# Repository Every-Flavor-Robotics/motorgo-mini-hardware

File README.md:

# motorgo-mini-hardware
## This repo is the home of the hardware revisions for the MotorGo-mini!
### This is a condensed and specialized version of the MotorGo-Mini, featuring:
- Esp32s3 based system, compatible with ESPIDF or Arduino
- Wifi + BT
- Single channel of motor control
- Integrated MT6701 magenetic encoder on back of board
- DRV8316 TI motor controller with low-side current sense
- 3A continous 8A peak FOC motor controls
- RGB LED indicator
- USB PD x2 with power ORing to protect power sources
- 6P JST PH input: 5V-20V
- CAN bus over USB-C (experimental use of sideband signals in USB 3.2+)

### Its still in development, particularly USBPD seems to be malfunctioning.  But checkout the schematics, renders, use example, and photos of the real board!
### Full board Render:

### Example board + motor + rendering:

### Top Level Schematic (full color):

### USB Module Sub-Schematic:

### DRV8316 Sub-Schematic:

### RGB indicator:

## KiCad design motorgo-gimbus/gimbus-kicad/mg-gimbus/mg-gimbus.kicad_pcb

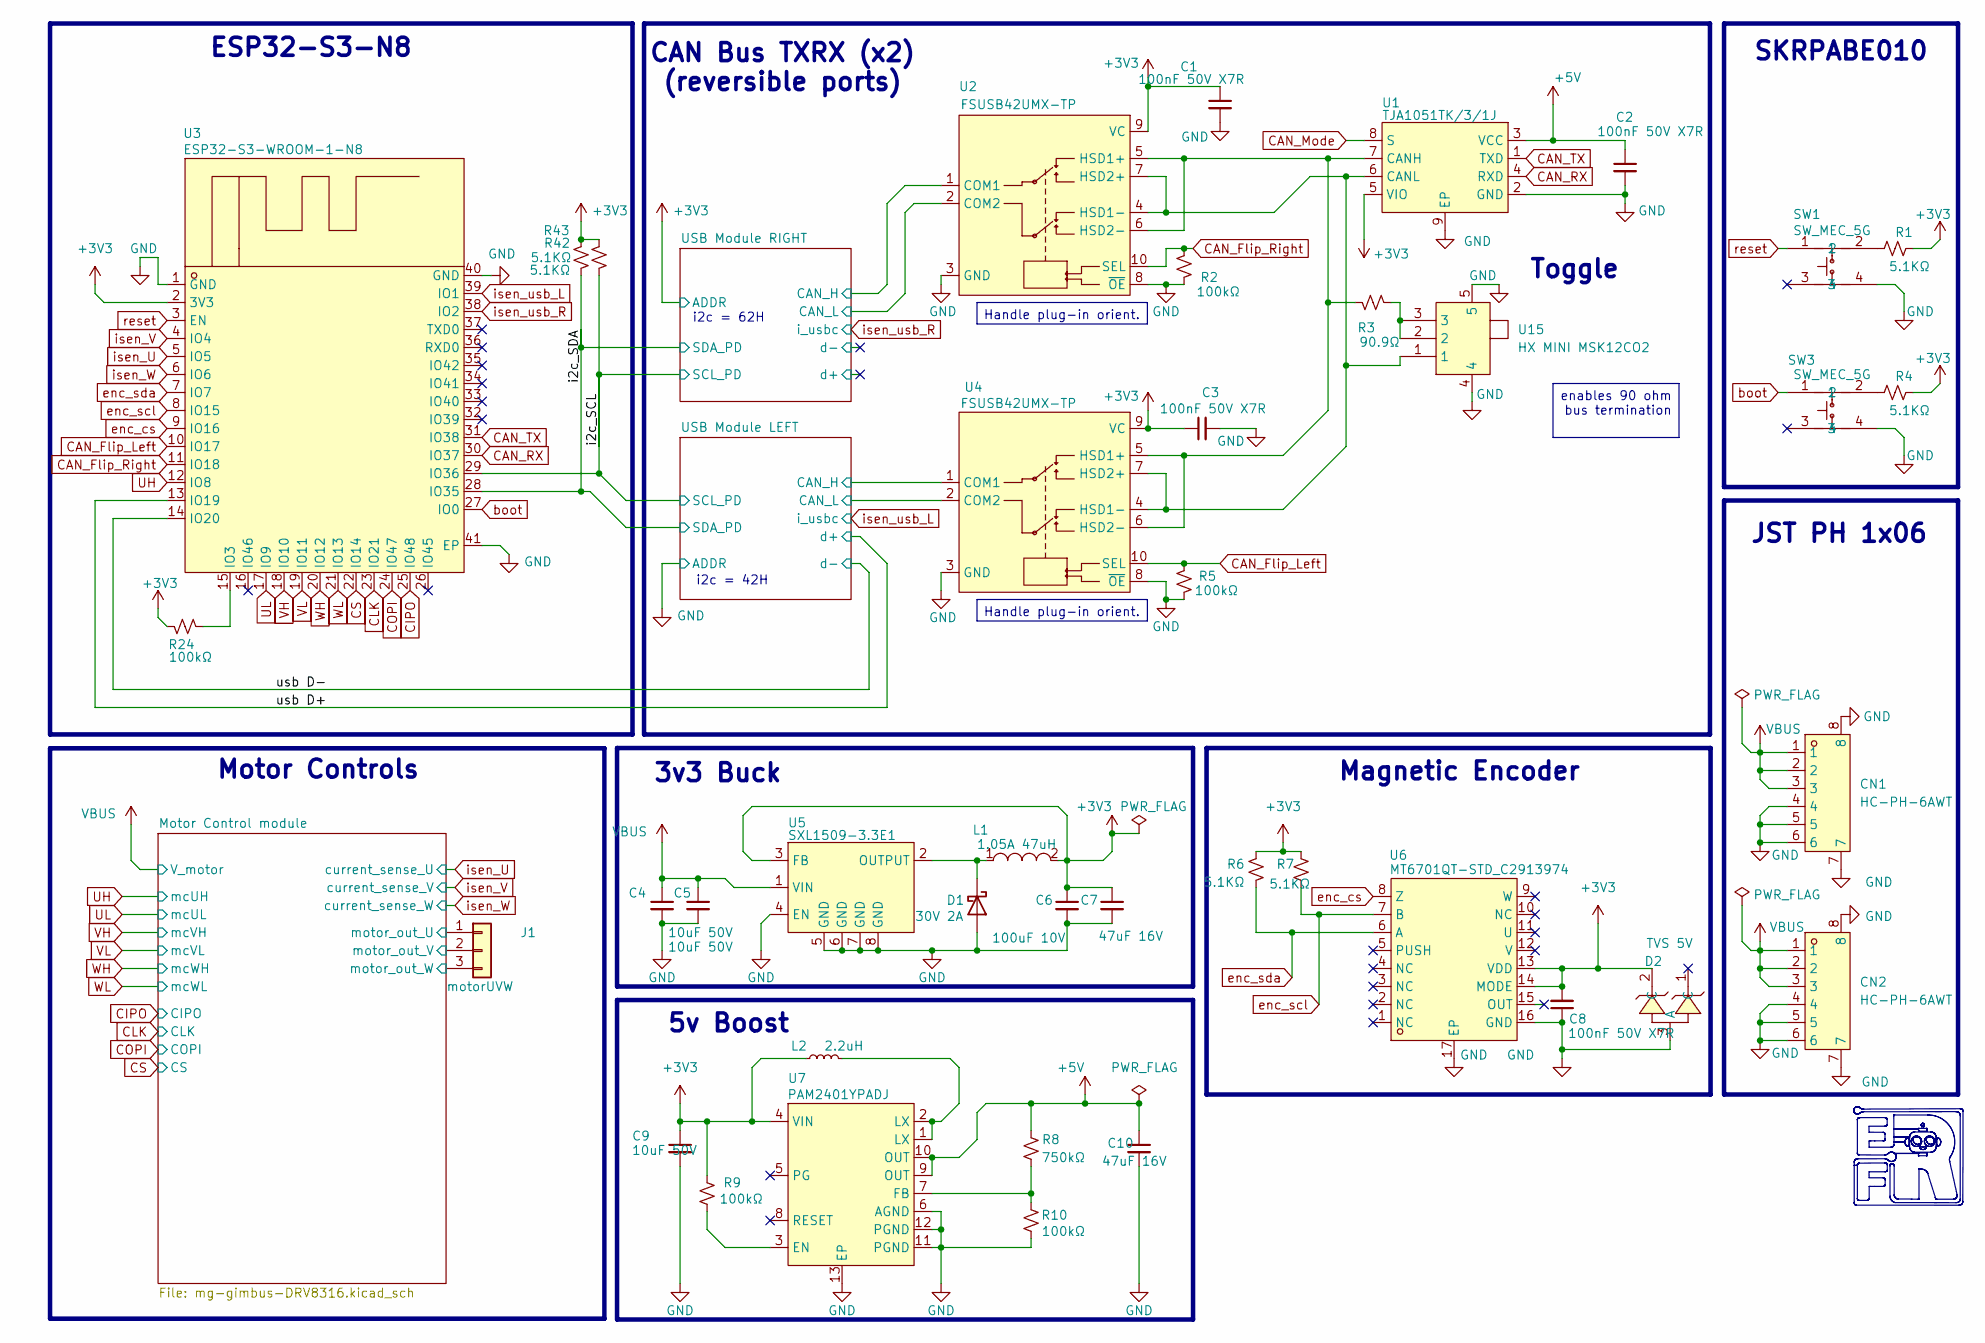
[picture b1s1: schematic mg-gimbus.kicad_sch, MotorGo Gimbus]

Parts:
C1, C2, C3, C8: 100nF 50V X7R; C_0402_1005Metric; LCSC Part C152814
C4, C5, C9: 10uF 50V; C_1206_3216Metric; LCSC Part C13585
C6: 100uF 10V; CAP-SMD_L7.3-W4.3_SA11CM470A19R55XXX; LCSC Part C42400366
C7, C10: 47uF 16V; C_1206_3216Metric; LCSC Part C172351
CN1, CN2: HC-PH-6AWT; CONN-SMD_6P-P2.00_HCTL_HC-PH-6AWT; LCSC Part C2845446
D1: 30V 2A; D_0603_1608Metric; LCSC Part C35621074
D2: TVS 5V; SOT-723_L1.2-W0.8-P0.40-LS1.2-BR; LCSC Part C896625
J1: motorUVW; Gimbus_Motor; LCSC Part n/a
L1: 1.05A 47uH; IND-SMD_L7.2-W6.6_GPSR07X0; LCSC Part C2929441
L2: 2.2uH; L_1008_2520Metric; LCSC Part C86092
R1, R4, R6, R7, R42, R43: 5.1KΩ; R_0402_1005Metric; LCSC Part C25905
R2, R5, R9, R10, R24: 100kΩ; R_0402_1005Metric; LCSC Part C25741
R3: 90.9Ω; R_0402_1005Metric; LCSC Part C208954
R8: 750kΩ; R_0402_1005Metric; LCSC Part C43291
SW1, SW3: SW_MEC_5G; KEY-SMD_4P-L4.2-W3.2-P2.20-LS4.6; LCSC Part C115360
U1: TJA1051TK/3/1J; HVSON-8_L3.0-W3.0-P0.65-BL-EP; LCSC Part C2875699
U2, U4: FSUSB42UMX-TP; XQFN-10_L1.8-W1.4-P0.40-TL; LCSC Part C42370490
U3: ESP32-S3-WROOM-1-N8; WIFIM-SMD_ESP32-S3-WROOM-1-N8; LCSC Part C2913198
U5: SXL1509-3.3E1; SOP-8_L4.9-W3.9-P1.27-LS6.0-BL-1; LCSC Part C33960106
U6: MT6701QT-STD_C2913974; QFN-16_L3.0-W3.0-P0.50-TL-EP1.7; LCSC Part C2913974
U7: PAM2401YPADJ; WDFN-12_L3.0-W3.0-P0.45-BL-EP; LCSC Part C490380
U15: HX MINI MSK12CO2; SW-SMD_MSK12CO2; LCSC Part C5149840

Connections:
+3V3: C1.1, C3.1, C6.1, C7.1, C8.2, C9.1, D2.2 (C), L1.2, L2.1, R1.2, R4.2, R6.1, R7.1, R9.2, R24.2, R42.1, R43.1, U1.5 (VIO), U2.9 (VC), U3.2 (3V3), U4.9 (VC), U5.3 (FB), U6.13 (VDD), U6.14 (MODE), U7.4 (VIN); also elsewhere on the board
+5V: C2.1, C10.1, R8.2, U1.3 (VCC), U7.9 (OUT), U7.10 (OUT)
/Motor Control module/motor_out_U: J1.1; also elsewhere on the board
/Motor Control module/motor_out_V: J1.2; also elsewhere on the board
/Motor Control module/motor_out_W: J1.3; also elsewhere on the board
/USB Module LEFT/CAN_H: U4.1 (COM1); also elsewhere on the board
/USB Module LEFT/CAN_L: U4.2 (COM2); also elsewhere on the board
/USB Module RIGHT/CAN_H: U2.1 (COM1); also elsewhere on the board
/USB Module RIGHT/CAN_L: U2.2 (COM2); also elsewhere on the board
/i2c_SCL: R42.2, U3.29 (IO36); also elsewhere on the board
/i2c_SDA: R43.2, U3.28 (IO35); also elsewhere on the board
/usb D+: U3.13 (IO19); also elsewhere on the board
/usb D-: U3.14 (IO20); also elsewhere on the board
CAN_Flip_Left: R5.2, U3.10 (IO17), U4.10 (SEL)
CAN_Flip_Right: R2.2, U2.10 (SEL), U3.11 (IO18)
CAN_Mode: U1.8 (S)
CAN_RX: U1.4 (RXD), U3.30 (IO37)
CAN_TX: U1.1 (TXD), U3.31 (IO38)
CIPO: U3.25 (IO48); also elsewhere on the board
CLK: U3.23 (IO21); also elsewhere on the board
COPI: U3.24 (IO47); also elsewhere on the board
CS: U3.22 (IO14); also elsewhere on the board
GND: C1.2, C2.2, C3.2, C4.2, C5.2, C6.2, C7.2, C8.1, C9.2, C10.2, CN1.4, CN1.5, CN1.6, CN1.7, CN1.8, CN2.4, CN2.5, CN2.6, CN2.7, CN2.8, D1.2 (A), D2.3 (A), R2.1, R5.1, R10.1, SW1.4, SW3.4, U1.2 (GND), U1.9 (EP), U2.3 (GND), U2.8 (~OE), U3.1 (GND), U3.40 (GND), U3.41 (EP), U4.3 (GND), U4.8 (~OE), U5.4 (EN), U5.5 (GND), U5.6 (GND), U5.7 (GND), U5.8 (GND), U6.16 (GND), U6.17 (EP), U7.6 (AGND), U7.11 (PGND), U7.12 (PGND), U7.13 (EP), U15.4, U15.5; also elsewhere on the board
unnamed: D1.1 (K), L1.1, U5.2 (OUTPUT)
unnamed: L2.2, U7.1 (LX), U7.2 (LX)
unnamed: R1.1, SW1.2
unnamed: R3.2, U15.2, U15.3
unnamed: R4.1, SW3.2
unnamed: R3.1, U1.7 (CANH), U2.5 (HSD1+), U2.6 (HSD2-), U4.5 (HSD1+), U4.6 (HSD2-)
unnamed: U1.6 (CANL), U2.4 (HSD1-), U2.7 (HSD2+), U4.4 (HSD1-), U4.7 (HSD2+), U15.1
unnamed: R24.1, U3.15 (IO3)
unnamed: R9.1, U7.3 (EN)
unnamed: R8.1, R10.2, U7.7 (FB)
UH: U3.12 (IO8); also elsewhere on the board
UL: U3.17 (IO9); also elsewhere on the board
VBUS: C4.1, C5.1, CN1.1, CN1.2, CN1.3, CN2.1, CN2.2, CN2.3, U5.1 (VIN); also elsewhere on the board
VH: U3.18 (IO10); also elsewhere on the board
VL: U3.19 (IO11); also elsewhere on the board
WH: U3.20 (IO12); also elsewhere on the board
WL: U3.21 (IO13); also elsewhere on the board
boot: SW3.1, U3.27 (IO0)
enc_cs: U3.9 (IO16), U6.8 (Z)
enc_scl: R7.2, U3.8 (IO15), U6.7 (B)
enc_sda: R6.2, U3.7 (IO7), U6.6 (A)
isen_U: U3.5 (IO5); also elsewhere on the board
isen_V: U3.4 (IO4); also elsewhere on the board
isen_W: U3.6 (IO6); also elsewhere on the board
isen_usb_L: U3.39 (IO1); also elsewhere on the board
isen_usb_R: U3.38 (IO2); also elsewhere on the board
reset: SW1.1, U3.3 (EN)

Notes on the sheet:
i2c = 62H
ESP32-S3-N8
i2c = 42H
Toggle
JST PH 1x06
Magnetic Encoder
5v Boost
SKRPABE010
CAN Bus TXRX (x2) (reversible ports)
3v3 Buck
Motor Controls
Handle plug-in orient.
enables 90 ohm bus termination

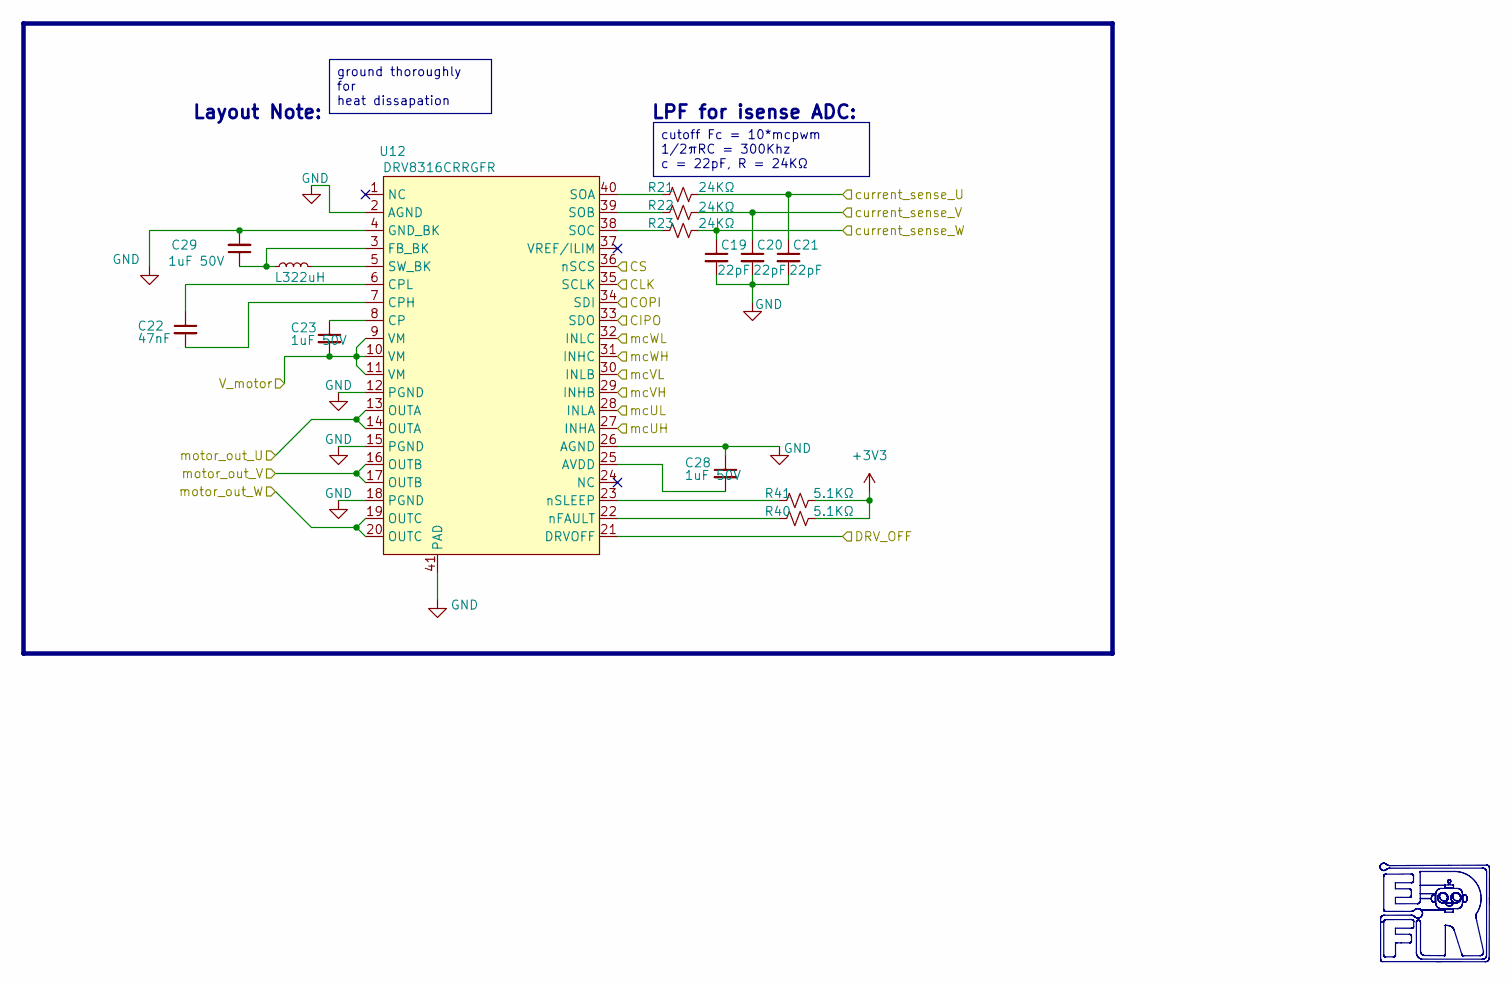
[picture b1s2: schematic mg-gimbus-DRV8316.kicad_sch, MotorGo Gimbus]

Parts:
C19, C20, C21: 22pF; C_0402_1005Metric; LCSC Part C76960
C22: 47nF; C_0402_1005Metric; LCSC Part C82219
C23, C28, C29: 1uF 50V; C_0805_2012Metric; LCSC Part C28323
L3: 22uH; L_0603_1608Metric; LCSC Part C383393
R21, R22, R23: 24KΩ; R_0402_1005Metric; LCSC Part C25769
R40, R41: 5.1KΩ; R_0402_1005Metric; LCSC Part C25905
U12: DRV8316CRRGFR; VQFN-40_L7.0-W5.0-P0.50-BL-EP5.7; LCSC Part C5447274

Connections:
+3V3: R40.2, R41.2; also elsewhere on the board
/Motor Control module/DRV_OFF: U12.21 (DRVOFF)
/Motor Control module/motor_out_U: U12.13 (OUTA), U12.14 (OUTA); also elsewhere on the board
/Motor Control module/motor_out_V: U12.16 (OUTB), U12.17 (OUTB); also elsewhere on the board
/Motor Control module/motor_out_W: U12.19 (OUTC), U12.20 (OUTC); also elsewhere on the board
CIPO: U12.33 (SDO); also elsewhere on the board
CLK: U12.35 (SCLK); also elsewhere on the board
COPI: U12.34 (SDI); also elsewhere on the board
CS: U12.36 (nSCS); also elsewhere on the board
GND: C19.2, C20.2, C21.2, C28.1, C29.2, U12.2 (AGND), U12.4 (GND_BK), U12.12 (PGND), U12.15 (PGND), U12.18 (PGND), U12.26 (AGND), U12.41 (PAD); also elsewhere on the board
unnamed: C28.2, U12.25 (AVDD)
unnamed: C23.1, U12.8 (CP)
unnamed: C22.2, U12.7 (CPH)
unnamed: C22.1, U12.6 (CPL)
unnamed: C29.1, L3.1, U12.3 (FB_BK)
unnamed: R21.1, U12.40 (SOA)
unnamed: R22.1, U12.39 (SOB)
unnamed: R23.1, U12.38 (SOC)
unnamed: L3.2, U12.5 (SW_BK)
unnamed: R40.1, U12.22 (nFAULT)
unnamed: R41.1, U12.23 (nSLEEP)
UH: U12.27 (INHA); also elsewhere on the board
UL: U12.28 (INLA); also elsewhere on the board
VBUS: C23.2, U12.9 (VM), U12.10 (VM), U12.11 (VM); also elsewhere on the board
VH: U12.29 (INHB); also elsewhere on the board
VL: U12.30 (INLB); also elsewhere on the board
WH: U12.31 (INHC); also elsewhere on the board
WL: U12.32 (INLC); also elsewhere on the board
isen_U: C21.1, R21.2; also elsewhere on the board
isen_V: C20.1, R22.2; also elsewhere on the board
isen_W: C19.1, R23.2; also elsewhere on the board

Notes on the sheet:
Layout Note:
LPF for isense ADC:
cutoff Fc = 10*mcpwm 1/2πRC = 300Khz c = 22pF, R = 24KΩ
ground thoroughly for heat dissapation

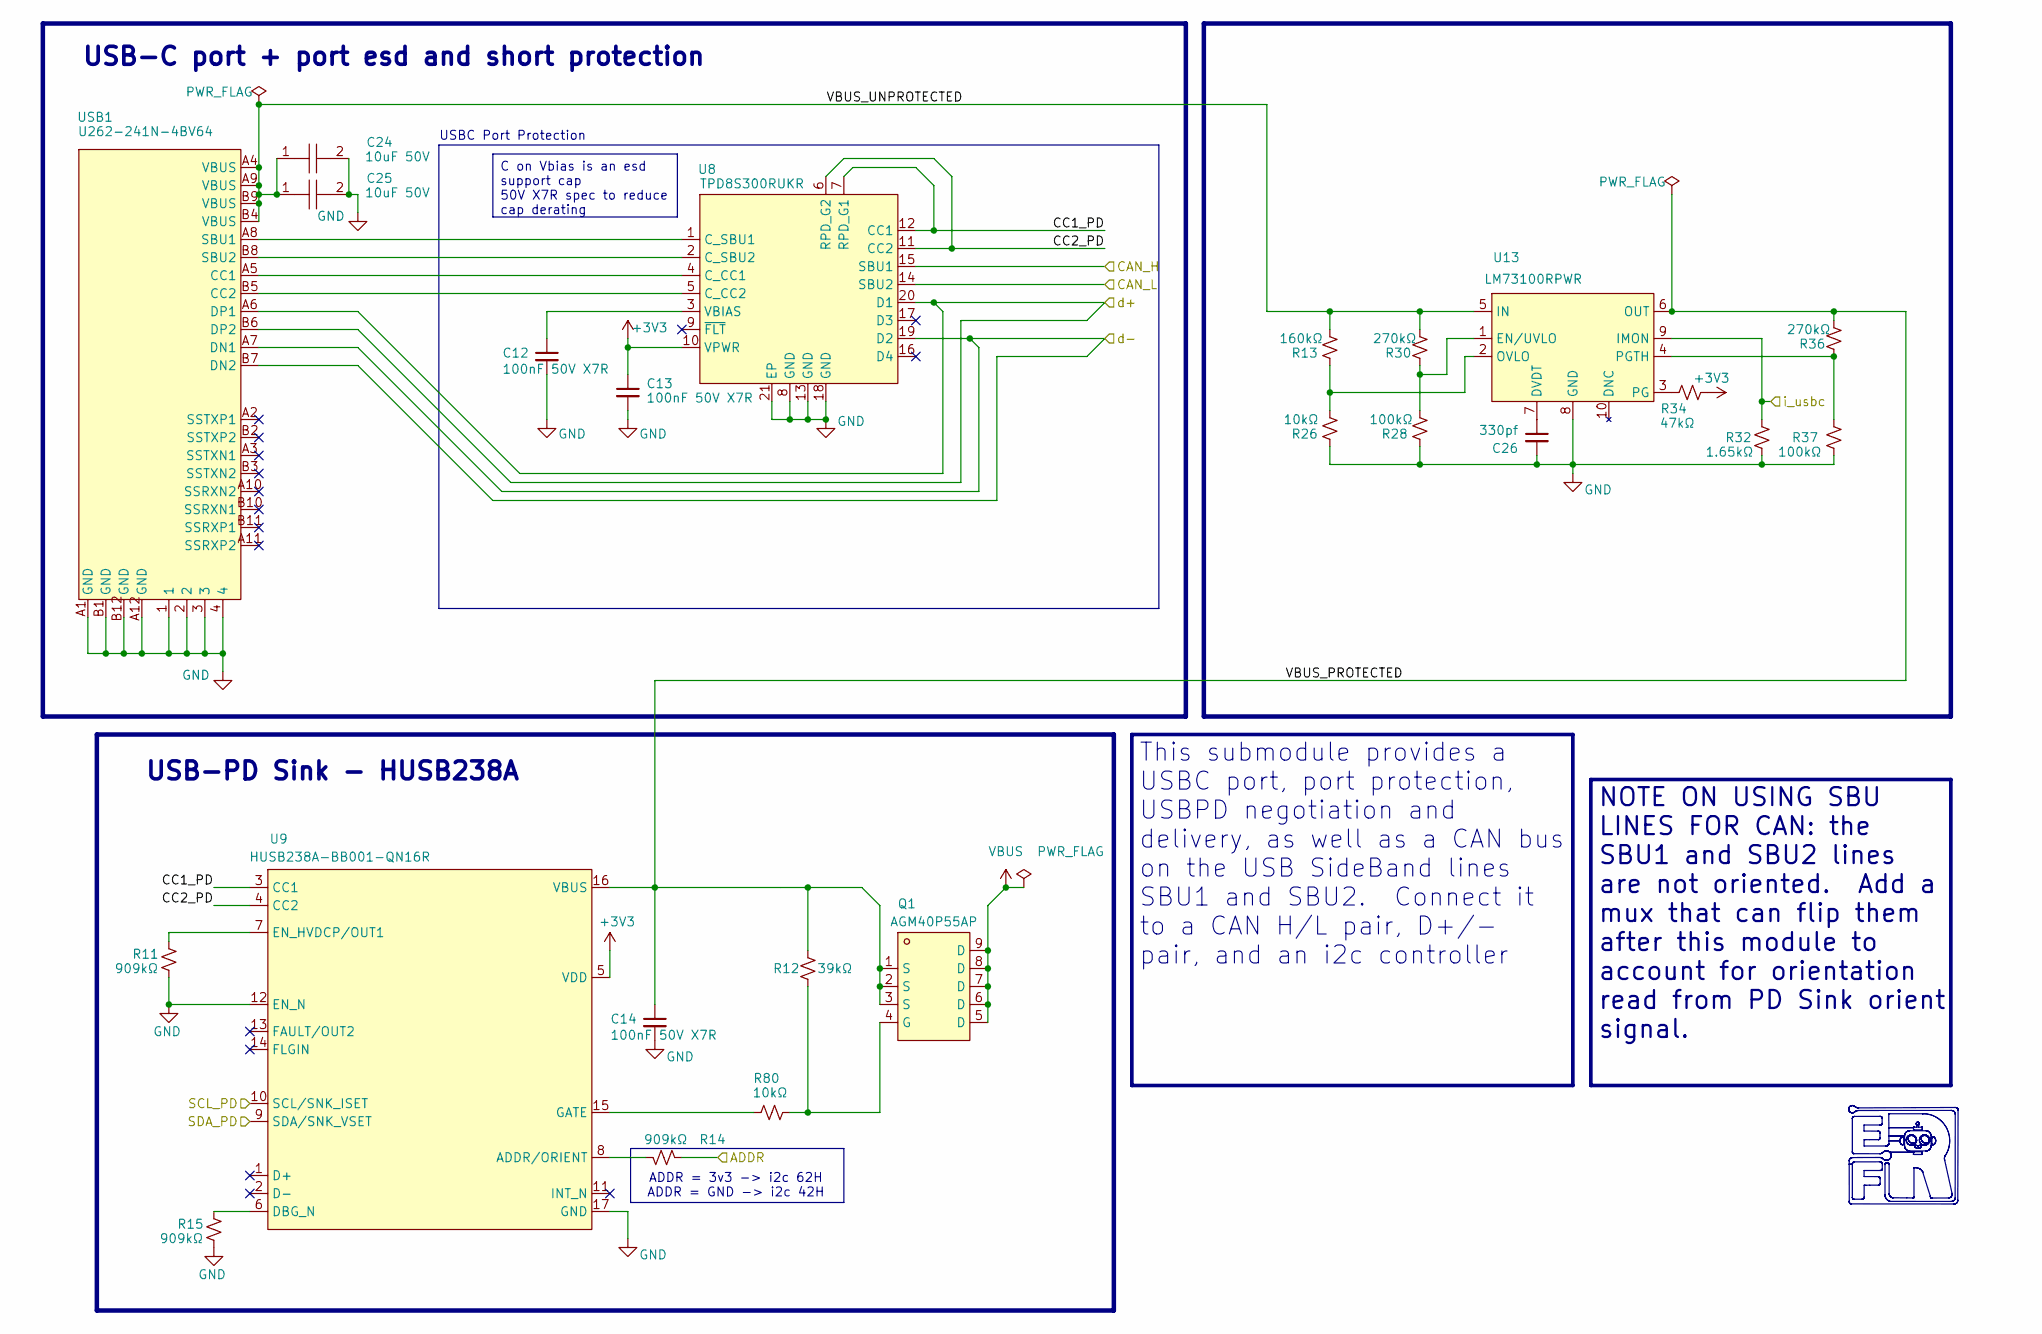
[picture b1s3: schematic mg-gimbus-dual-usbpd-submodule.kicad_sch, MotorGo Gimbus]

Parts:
C12, C13, C14: 100nF 50V X7R; C_0402_1005Metric; LCSC Part C152814
C24, C25: 10uF 50V; C_1206_3216Metric; LCSC Part C13585
C26: 330pf; C_0402_1005Metric; LCSC Part C13533
Q1: AGM40P55AP; DFN-8_L3.3-W3.3-P0.65-BL-3; LCSC Part C5340112
R11, R14, R15: 909kΩ; R_0402_1005Metric; LCSC Part C25799
R12: 39kΩ; R_0402_1005Metric; LCSC Part C25783
R13: 160kΩ; R_0402_1005Metric; LCSC Part C25757
R26, R80: 10kΩ; R_0402_1005Metric; LCSC Part C25744
R28, R37: 100kΩ; R_0402_1005Metric; LCSC Part C25741
R30, R36: 270kΩ; R_0402_1005Metric; LCSC Part C25770
R32: 1.65kΩ; R_0402_1005Metric; LCSC Part C25869
R34: 47kΩ; R_0402_1005Metric; LCSC Part C25792
U8: TPD8S300RUKR; WQFN-20_L3.0-W3.0-P0.40-TL-EP; LCSC Part C571205
U9: HUSB238A-BB001-QN16R; QFN-16_L3.0-W3.0-P0.50-BL-EP1.7; LCSC Part C24833806
U13: LM73100RPWR; VQFN-10_L2.0-W2.0-P0.45-TL; LCSC Part C3210761
USB1: U262-241N-4BV64; USB-C-SMD_TYC-324G; LCSC Part C388660

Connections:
+3V3: C13.1, R14.2, R34.1, U8.10 (VPWR), U9.5 (VDD); also elsewhere on the board
/USB Module RIGHT/CAN_H: U8.15 (SBU1); also elsewhere on the board
/USB Module RIGHT/CAN_L: U8.14 (SBU2); also elsewhere on the board
/USB Module RIGHT/CC1_PD: U8.7 (RPD_G1), U8.12 (CC1), U9.3 (CC1)
/USB Module RIGHT/CC2_PD: U8.6 (RPD_G2), U8.11 (CC2), U9.4 (CC2)
/USB Module RIGHT/VBUS_PROTECTED: C14.1, Q1.1 (S), Q1.2 (S), Q1.3 (S), R12.2, R36.2, U9.16 (VBUS), U13.6 (OUT)
/USB Module RIGHT/VBUS_UNPROTECTED: C24.1, C25.1, R13.2, R30.2, U13.5 (IN), USB1.A4 (VBUS), USB1.A9 (VBUS), USB1.B4 (VBUS), USB1.B9 (VBUS)
/USB Module RIGHT/d+: U8.20 (D1), USB1.A6 (DP1), USB1.B6 (DP2)
/USB Module RIGHT/d-: U8.19 (D2), USB1.A7 (DN1), USB1.B7 (DN2)
/i2c_SCL: U9.10 (SCL/SNK_ISET); also elsewhere on the board
/i2c_SDA: U9.9 (SDA/SNK_VSET); also elsewhere on the board
GND: C12.2, C13.2, C14.2, C24.2, C25.2, C26.2, R11.1, R15.1, R26.1, R28.1, R32.1, R37.1, U8.8 (GND), U8.13 (GND), U8.18 (GND), U8.21 (EP), U9.12 (EN_N), U9.17 (GND), U13.8 (GND), USB1.1, USB1.2, USB1.3, USB1.4, USB1.A1 (GND), USB1.A12 (GND), USB1.B1 (GND), USB1.B12 (GND); also elsewhere on the board
unnamed: Q1.4 (G), R12.1, R80.2
unnamed: U8.4 (C_CC1), USB1.A5 (CC1)
unnamed: U8.5 (C_CC2), USB1.B5 (CC2)
unnamed: U8.1 (C_SBU1), USB1.A8 (SBU1)
unnamed: U8.2 (C_SBU2), USB1.B8 (SBU2)
unnamed: C12.1, U8.3 (VBIAS)
unnamed: R14.1, U9.8 (ADDR/ORIENT)
unnamed: R15.2, U9.6 (DBG_N)
unnamed: R11.2, U9.7 (EN_HVDCP/OUT1)
unnamed: R80.1, U9.15 (GATE)
unnamed: C26.1, U13.7 (DVDT)
unnamed: R28.2, R30.1, U13.1 (EN/UVLO)
unnamed: R13.1, R26.2, U13.2 (OVLO)
unnamed: R34.2, U13.3 (PG)
unnamed: R36.1, R37.2, U13.4 (PGTH)
VBUS: Q1.5 (D), Q1.6 (D), Q1.7 (D), Q1.8 (D), Q1.9 (D); also elsewhere on the board
isen_usb_R: R32.2, U13.9 (IMON); also elsewhere on the board

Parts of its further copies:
C11, C15: 10uF 50V; C_1206_3216Metric; LCSC Part C13585
C16, C17, C18: 100nF 50V X7R; C_0402_1005Metric; LCSC Part C152814
C27: 330pf; C_0402_1005Metric; LCSC Part C13533
Q2: AGM40P55AP; DFN-8_L3.3-W3.3-P0.65-BL-3; LCSC Part C5340112
R16, R19, R20: 909kΩ; R_0402_1005Metric; LCSC Part C25799
R17: 39kΩ; R_0402_1005Metric; LCSC Part C25783
R18, R27: 10kΩ; R_0402_1005Metric; LCSC Part C25744
R25: 160kΩ; R_0402_1005Metric; LCSC Part C25757
R29, R39: 100kΩ; R_0402_1005Metric; LCSC Part C25741
R31, R38: 270kΩ; R_0402_1005Metric; LCSC Part C25770
R33: 1.65kΩ; R_0402_1005Metric; LCSC Part C25869
R35: 47kΩ; R_0402_1005Metric; LCSC Part C25792
U10: TPD8S300RUKR; WQFN-20_L3.0-W3.0-P0.40-TL-EP; LCSC Part C571205
U11: HUSB238A-BB001-QN16R; QFN-16_L3.0-W3.0-P0.50-BL-EP1.7; LCSC Part C24833806
U14: LM73100RPWR; VQFN-10_L2.0-W2.0-P0.45-TL; LCSC Part C3210761
USB2: U262-241N-4BV64; USB-C-SMD_TYC-324G; LCSC Part C388660

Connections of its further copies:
+3V3: C17.1, R35.1, U10.10 (VPWR), U11.5 (VDD); also elsewhere on the board
/USB Module LEFT/CAN_H: U10.15 (SBU1); also elsewhere on the board
/USB Module LEFT/CAN_L: U10.14 (SBU2); also elsewhere on the board
/USB Module LEFT/CC1_PD: U10.7 (RPD_G1), U10.12 (CC1), U11.3 (CC1)
/USB Module LEFT/CC2_PD: U10.6 (RPD_G2), U10.11 (CC2), U11.4 (CC2)
/USB Module LEFT/VBUS_PROTECTED: C18.1, Q2.1 (S), Q2.2 (S), Q2.3 (S), R17.2, R38.2, U11.16 (VBUS), U14.6 (OUT)
/USB Module LEFT/VBUS_UNPROTECTED: C11.1, C15.1, R25.2, R31.2, U14.5 (IN), USB2.A4 (VBUS), USB2.A9 (VBUS), USB2.B4 (VBUS), USB2.B9 (VBUS)
/i2c_SCL: U11.10 (SCL/SNK_ISET); also elsewhere on the board
/i2c_SDA: U11.9 (SDA/SNK_VSET); also elsewhere on the board
/usb D+: U10.20 (D1), USB2.A6 (DP1), USB2.B6 (DP2); also elsewhere on the board
/usb D-: U10.19 (D2), USB2.A7 (DN1), USB2.B7 (DN2); also elsewhere on the board
GND: C11.2, C15.2, C16.2, C17.2, C18.2, C27.2, R16.1, R19.2, R20.1, R27.1, R29.1, R33.1, R39.1, U10.8 (GND), U10.13 (GND), U10.18 (GND), U10.21 (EP), U11.12 (EN_N), U11.17 (GND), U14.8 (GND), USB2.1, USB2.2, USB2.3, USB2.4, USB2.A1 (GND), USB2.A12 (GND), USB2.B1 (GND), USB2.B12 (GND); also elsewhere on the board
unnamed: Q2.4 (G), R17.1, R18.2
unnamed: U10.4 (C_CC1), USB2.A5 (CC1)
unnamed: U10.5 (C_CC2), USB2.B5 (CC2)
unnamed: U10.1 (C_SBU1), USB2.A8 (SBU1)
unnamed: U10.2 (C_SBU2), USB2.B8 (SBU2)
unnamed: C16.1, U10.3 (VBIAS)
unnamed: R19.1, U11.8 (ADDR/ORIENT)
unnamed: R20.2, U11.6 (DBG_N)
unnamed: R16.2, U11.7 (EN_HVDCP/OUT1)
unnamed: R18.1, U11.15 (GATE)
unnamed: C27.1, U14.7 (DVDT)
unnamed: R29.2, R31.1, U14.1 (EN/UVLO)
unnamed: R25.1, R27.2, U14.2 (OVLO)
unnamed: R35.2, U14.3 (PG)
unnamed: R38.1, R39.2, U14.4 (PGTH)
VBUS: Q2.5 (D), Q2.6 (D), Q2.7 (D), Q2.8 (D), Q2.9 (D); also elsewhere on the board
isen_usb_L: R33.2, U14.9 (IMON); also elsewhere on the board

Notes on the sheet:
ADDR = 3v3 -> i2c 62H ADDR = GND -> i2c 42H
USB-C port + port esd and short protection
USBC Port Protection
USB-PD Sink - HUSB238A
C on Vbias is an esd support cap 50V X7R spec to reduce cap derating
NOTE ON USING SBU LINES FOR CAN: the SBU1 and SBU2 lines are not oriented. Add a mux that can flip them after this module to account for orientation read from PD Sink orient signal.
This submodule provides a USBC port, port protection, USBPD negotiation and delivery, as well as a CAN bus on the USB SideBand lines SBU1 and SBU2. Connect it to a CAN H/L pair, D+/- pair, and an i2c controller

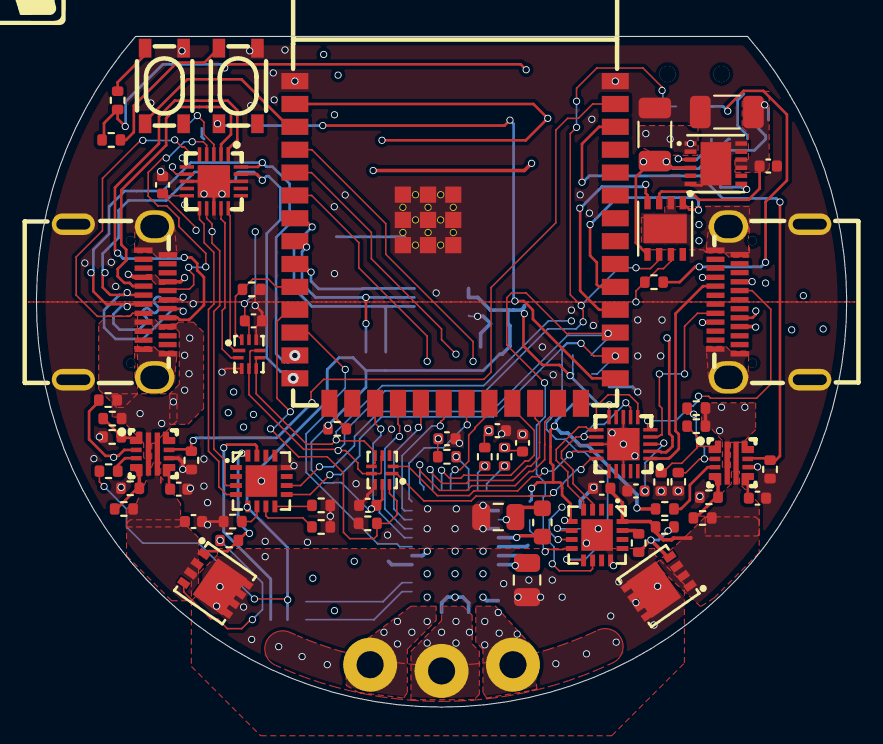
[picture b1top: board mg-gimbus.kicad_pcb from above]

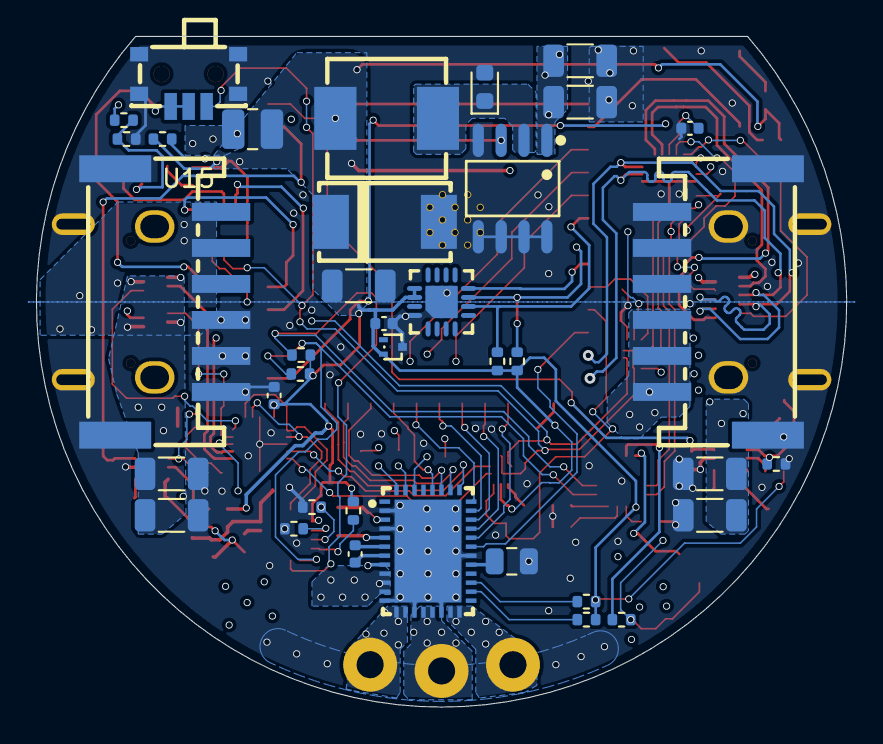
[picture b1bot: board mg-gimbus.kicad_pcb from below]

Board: 4 copper layers, 45.0 x 37.3 mm, 102 parts (38 on the bottom side), 100 nets.
